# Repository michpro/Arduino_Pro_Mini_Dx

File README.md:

# **Arduino Pro Mini Dx Module**

- [**Arduino Pro Mini Dx Module**](#arduino-pro-mini-dx-module)
  - [**General info**](#general-info)
  - [**Hardware**](#hardware)
  - [**Software**](#software)
  - [**Reporting bugs**](#reporting-bugs)
  - [**License**](#license)
  - [**Support**](#support)

---

## **General info**
Through the use of the Arduino Pro Mini form factor PCB, this module allows easy replacement of modules based on the ATmega328P processor with modern solutions from the AVR Dx family. This allows a significant increase in program size (up to 128kB FLASH) and the use of many new peripherals.

---

## **Hardware**
The module dispenses with the use of an external high-frequency resonator. The clocking of the uC is generated by an internal RC resonator. It has sufficient accuracy for most applications, which can be further improved by internal calibration using the mounted RTC resonator (32768 Hz). This also allows the uC's clock frequency to be changed even during programme execution.<br>
A dedicated voltage regulator has also been dispensed with, as the uCs of the AVR Dx family operate stably over the full supply voltage range: 1.8-5.5V with a maximum clock frequency of 24MHz.<br><br>
Below is a schematic diagram:<br>

<br>
and visualisation of the module (click picture):
<p align="center"></p>

The production files can be found in the location: https://github.com/michpro/Arduino_Pro_Mini_Dx/blob/master/production/

---

## **Software**
The module can be used with any toolchain:
 - Arduino, PlatformIO - [SpenceKonde - DxCore](https://github.com/SpenceKonde/DxCore)
 - or Microchip Studio for AVR®.

The program code is uploaded to the module using the [UPDI programmer](https://github.com/SpenceKonde/DxCore?tab=readme-ov-file#updi-programming).

---

## **Reporting bugs**

[Create an issue on GitHub](https://github.com/michpro/Arduino_Pro_Mini_Dx/issues).

---

## **License**
Copyright © 2023-2025 Michal Protasowicki

Source: https://github.com/michpro/Arduino_Pro_Mini_Dx

This project is released under CERN Open Hardware Licence Version 2 - Permissive.

---

## **Support**
If You find my projects interesting and You wanted to support my work, You can give me a cup of coffee or a keg of beer :)

&nbsp;&nbsp;&nbsp;&nbsp;&nbsp;&nbsp;&nbsp;&nbsp;&nbsp;&nbsp;

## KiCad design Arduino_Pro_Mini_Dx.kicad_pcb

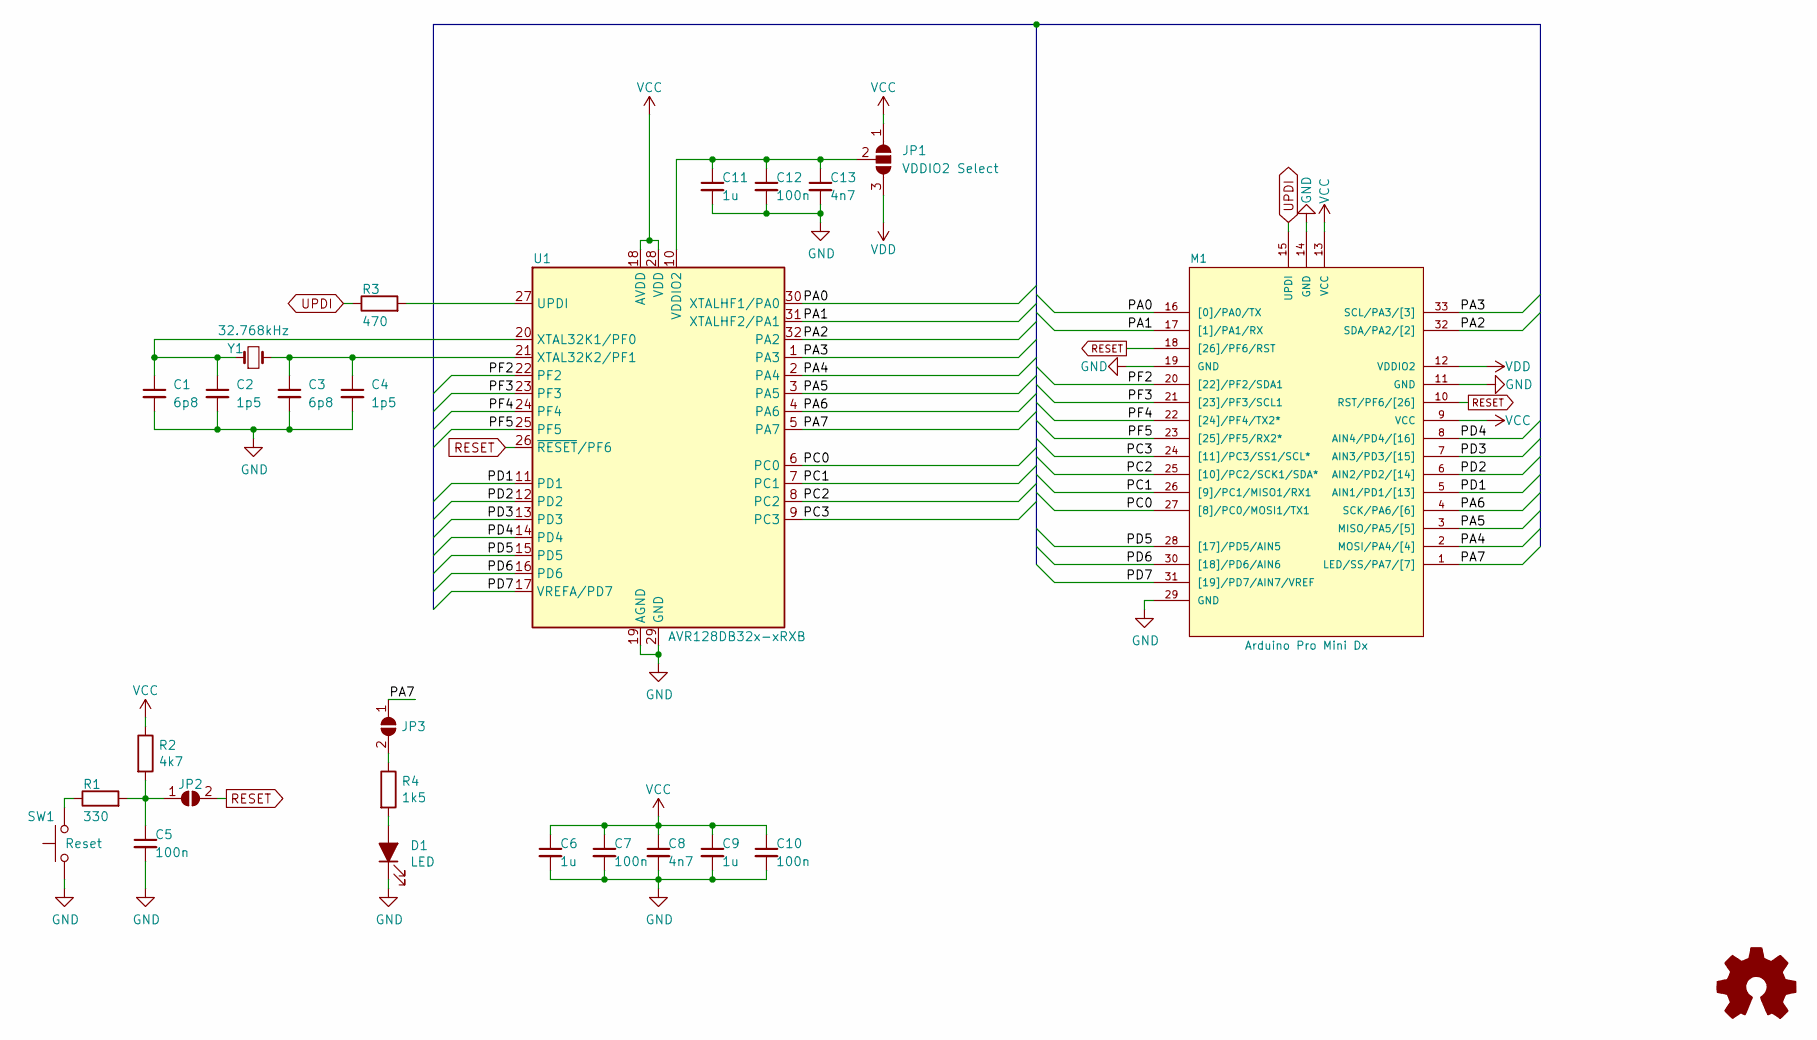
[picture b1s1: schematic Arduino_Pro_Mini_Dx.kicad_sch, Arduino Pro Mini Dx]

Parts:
C1, C3: 6p8; C_0402_1005Metric; LCSC C1576
C2, C4: 1p5; C_0402_1005Metric; LCSC C1552
C5, C7, C10, C12: 100n; C_0402_1005Metric; LCSC C1525
C6, C9, C11: 1u; C_0402_1005Metric; LCSC C52923
C8, C13: 4n7; C_0402_1005Metric; LCSC C1538
D1: LED; LED_0603_1608Metric; LCSC C2286
JP1: VDDIO2 Select; SolderJumper-3_P1.3mm_Open_RoundedPad1.0x1.5mm
JP2: RST; SolderJumper-2_P1.3mm_Open_TrianglePad1.0x1.5mm
JP3: LED; SolderJumper-2_P1.3mm_Open_TrianglePad1.0x1.5mm
LOGO1: Logo_Open_Hardware_Small; OSHW-Logo2_7.3x6mm_SilkScreen
M1: Arduino Pro Mini Dx; diy-modules-ARDUINO-PRO-MINI-Dx-BRD
R1: 330; R_0402_1005Metric; LCSC C25104
R2: 4k7; R_0402_1005Metric; LCSC C25900
R3: 470; R_0402_1005Metric; LCSC C25117
R4: 1k5; R_0402_1005Metric; LCSC C25867
SW1: Reset; TS-1088R-02526_SPST; LCSC C455281
U1: AVR128DB32x-xRXB; QFN-32-1EP_5x5mm_P0.5mm_EP3.1x3.1mm; LCSC C1518641
Y1: 32.768kHz; Crystal_SMD_3215-2Pin_3.2x1.5mm; LCSC C5830644

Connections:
/PA0: M1.16 ([0]/PA0/TX), U1.30 (XTALHF1/PA0)
/PA1: M1.17 ([1]/PA1/RX), U1.31 (XTALHF2/PA1)
/PA2: M1.32 (SDA/PA2/[2]), U1.32 (PA2)
/PA3: M1.33 (SCL/PA3/[3]), U1.1 (PA3)
/PA4: M1.2 (MOSI/PA4/[4]), U1.2 (PA4)
/PA5: M1.3 (MISO/PA5/[5]), U1.3 (PA5)
/PA6: M1.4 (SCK/PA6/[6]), U1.4 (PA6)
/PA7: JP3.1 (A), M1.1 (LED/SS/PA7/[7]), U1.5 (PA7)
/PC0: M1.27 ([8]/PC0/MOSI1/TX1), U1.6 (PC0)
/PC1: M1.26 ([9]/PC1/MISO1/RX1), U1.7 (PC1)
/PC2: M1.25 ([10]/PC2/SCK1/SDA*), U1.8 (PC2)
/PC3: M1.24 ([11]/PC3/SS1/SCL*), U1.9 (PC3)
/PD1: M1.5 (AIN1/PD1/[13]), U1.11 (PD1)
/PD2: M1.6 (AIN2/PD2/[14]), U1.12 (PD2)
/PD3: M1.7 (AIN3/PD3/[15]), U1.13 (PD3)
/PD4: M1.8 (AIN4/PD4/[16]), U1.14 (PD4)
/PD5: M1.28 ([17]/PD5/AIN5), U1.15 (PD5)
/PD6: M1.30 ([18]/PD6/AIN6), U1.16 (PD6)
/PD7: M1.31 ([19]/PD7/AIN7/VREF), U1.17 (VREFA/PD7)
/PF2: M1.20 ([22]/PF2/SDA1), U1.22 (PF2)
/PF3: M1.21 ([23]/PF3/SCL1), U1.23 (PF3)
/PF4: M1.22 ([24]/PF4/TX2*), U1.24 (PF4)
/PF5: M1.23 ([25]/PF5/RX2*), U1.25 (PF5)
GND: C1.2, C2.2, C3.2, C4.2, C5.2, C6.2, C7.2, C8.2, C9.2, C10.2, C11.2, C12.2, C13.2, D1.1 (K), M1.11 (GND), M1.14 (GND), M1.19 (GND), M1.29 (GND), SW1.1, U1.19 (AGND), U1.29 (GND), U1.33 (GND)
unnamed: D1.2 (A), R4.2
unnamed: C11.1, C12.1, C13.1, JP1.2 (C), U1.10 (VDDIO2)
unnamed: C5.1, JP2.1 (A), R1.2, R2.2
unnamed: JP3.2 (B), R4.1
unnamed: R1.1, SW1.2
unnamed: R3.2, U1.27 (UPDI)
unnamed: C1.1, C2.1, U1.20 (XTAL32K1/PF0), Y1.1
unnamed: C3.1, C4.1, U1.21 (XTAL32K2/PF1), Y1.2
RESET: JP2.2 (B), M1.10 (RST/PF6/[26]), M1.18 ([26]/PF6/RST), U1.26 (~RESET/PF6)
UPDI: M1.15 (UPDI), R3.1
VCC: C6.1, C7.1, C8.1, C9.1, C10.1, JP1.1 (A), M1.9 (VCC), M1.13 (VCC), R2.1, U1.18 (AVDD), U1.28 (VDD)
VDD: JP1.3 (B), M1.12 (VDDIO2)

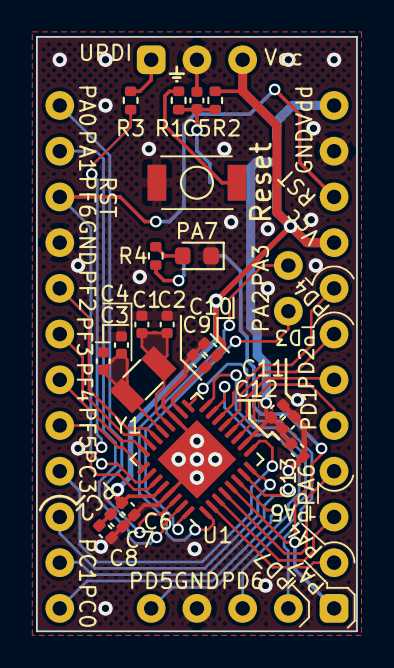
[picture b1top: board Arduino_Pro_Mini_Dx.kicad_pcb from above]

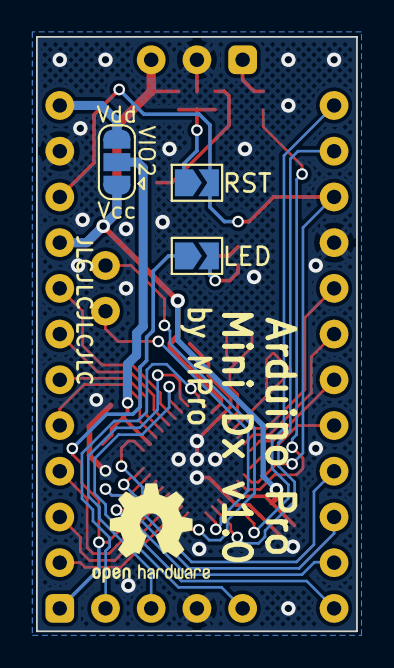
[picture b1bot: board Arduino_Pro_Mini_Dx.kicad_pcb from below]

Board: 2 copper layers, 17.8 x 33.0 mm, 26 parts (4 on the bottom side), 36 nets.

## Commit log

2025-01-04 functional revision
2025-01-17 3D online preview added
2025-04-06 project files updated to Kicad version 9.0.1

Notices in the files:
Arduino_Pro_Mini_Dx.kicad_pcb:
© 2023 MPro
Licensed under CERN-OHL-P v2 or any later version
